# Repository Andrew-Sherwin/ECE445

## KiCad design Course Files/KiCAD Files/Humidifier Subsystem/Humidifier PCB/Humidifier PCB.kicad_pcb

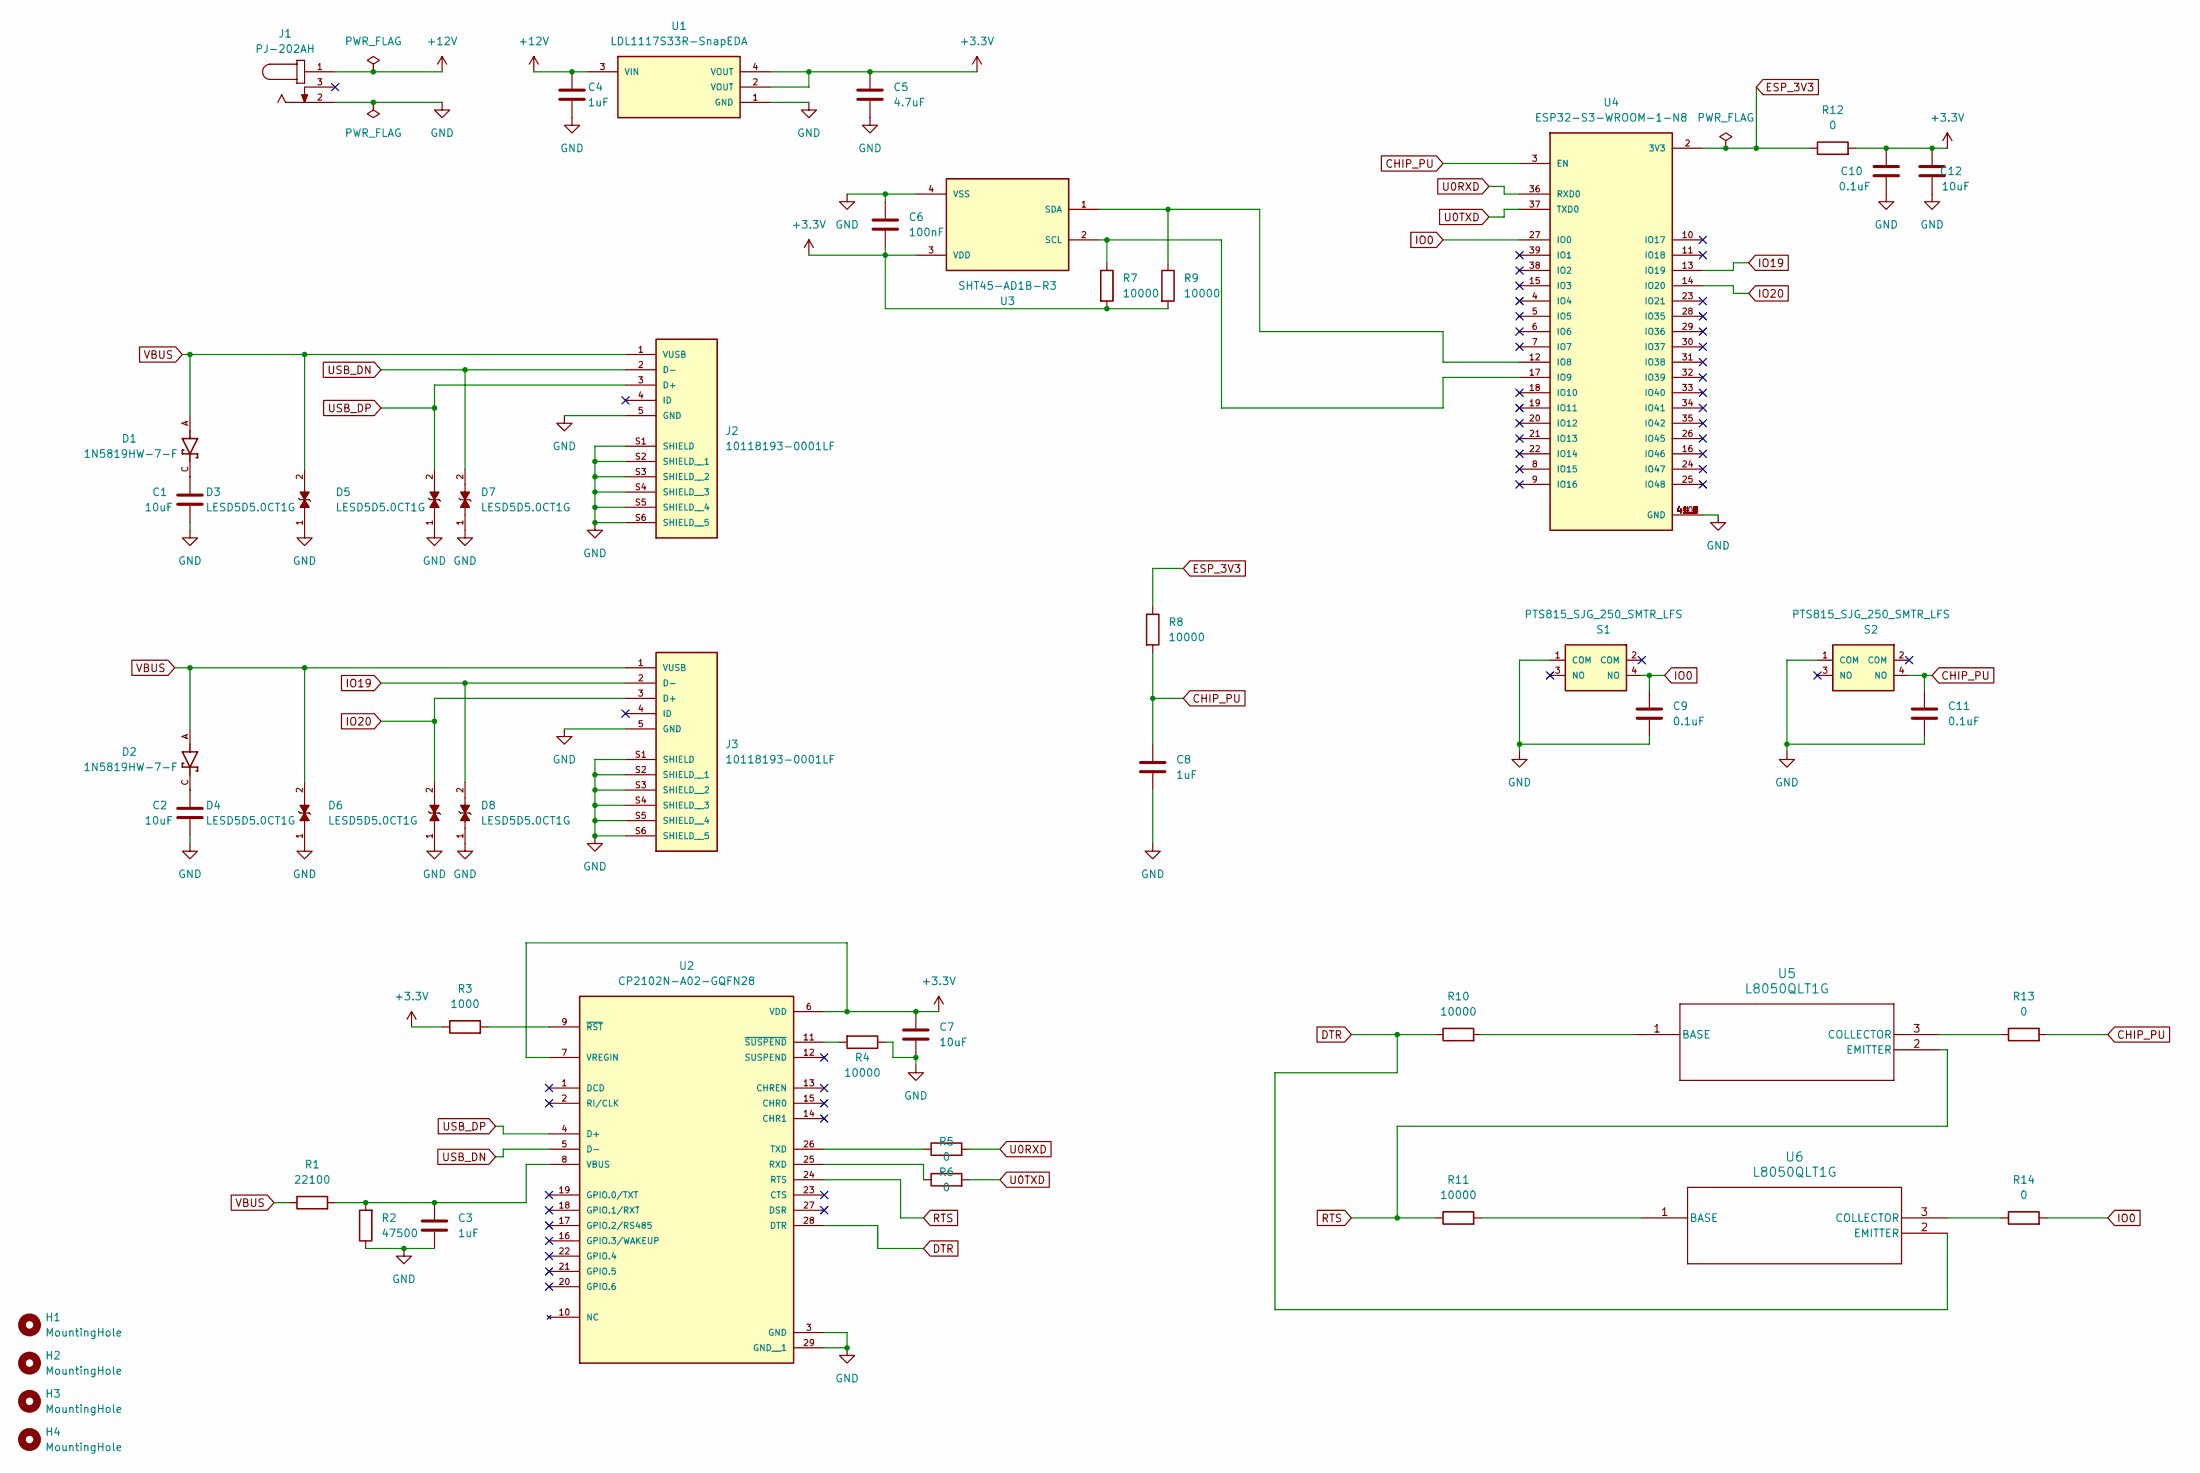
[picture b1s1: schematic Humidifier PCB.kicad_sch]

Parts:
C1, C2, C7, C12: 10uF
C3, C4, C8: 1uF
C5: 4.7uF
C6: 100nF
C9, C10, C11: 0.1uF
D1, D2: 1N5819HW-7-F; PARTREV 18-2
D3, D4, D5, D6, D7, D8: LESD5D5.0CT1G; PARTREV O
H1, H2, H3, H4: MountingHole
J1: PJ-202AH; PART_REV 1.02
J2, J3: 10118193-0001LF; PARTREV E
R1: 22100
R2: 47500
R3: 1000
R4, R7, R8, R9, R10, R11: 10000
R5, R6, R12, R13, R14: 0
S1, S2: PTS815_SJG_250_SMTR_LFS; MOUSER_PART_NUMBER 611-PTS815SJG250SMTR
U1: LDL1117S33R-SnapEDA; PARTREV 7; DigiKey_Part_Number 497-17239-2-ND
U2: CP2102N-A02-GQFN28; PARTREV 1.5
U3: SHT45-AD1B-R3
U4: ESP32-S3-WROOM-1-N8; DigiKey_Part_Number 1965-ESP32-S3-WROOM-1-N8TR-ND
U5, U6: L8050QLT1G

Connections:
+3.3V: C5.1, C6.2, C7.1, C10.1, C12.1, R3.1, R7.2, R9.2, R12.2, U1.2 (VOUT), U1.4 (VOUT), U2.6 (VDD), U2.7 (VREGIN), U3.3 (VDD)
+12V: C4.1, J1.1, U1.3 (VIN)
CHIP_PU: C8.1, C11.1, R8.2, R13.2, S2.4 (NO), U4.3 (EN)
DTR: R10.1, U2.28 (DTR), U6.2 (EMITTER)
ESP_3V3: R8.1, R12.1, U4.2 (3V3)
GND: C1.2, C2.2, C3.2, C4.2, C5.2, C6.1, C7.2, C8.2, C9.2, C10.2, C11.2, C12.2, D3.1, D4.1, D5.1, D6.1, D7.1, D8.1, J1.2, J2.5 (GND), J2.S1 (SHIELD), J2.S2 (SHIELD__1), J2.S3 (SHIELD__2), J2.S4 (SHIELD__3), J2.S5 (SHIELD__4), J2.S6 (SHIELD__5), J3.5 (GND), J3.S1 (SHIELD), J3.S2 (SHIELD__1), J3.S3 (SHIELD__2), J3.S4 (SHIELD__3), J3.S5 (SHIELD__4), J3.S6 (SHIELD__5), R2.1, R4.1, S1.1 (COM), S2.1 (COM), U1.1 (GND), U2.3 (GND), U2.29 (GND__1), U3.4 (VSS), U4.1 (GND), U4.40 (GND), U4.41_1 (GND), U4.41_2 (GND), U4.41_3 (GND), U4.41_4 (GND), U4.41_5 (GND), U4.41_6 (GND), U4.41_7 (GND), U4.41_8 (GND), U4.41_9 (GND)
IO0: C9.1, R14.2, S1.4 (NO), U4.27 (IO0)
IO19: D8.2, J3.2 (D-), U4.13 (IO19)
IO20: D6.2, J3.3 (D+), U4.14 (IO20)
unnamed: C1.1, D1.C
unnamed: C2.1, D2.C
unnamed: R6.1, U2.25 (RXD)
unnamed: R5.1, U2.26 (TXD)
unnamed: C3.1, R1.2, R2.2, U2.8 (VBUS)
unnamed: R3.2, U2.9 (~RST)
unnamed: R4.2, U2.11 (~SUSPEND)
unnamed: R7.1, U3.2 (SCL), U4.17 (IO9)
unnamed: R9.1, U3.1 (SDA), U4.12 (IO8)
unnamed: R10.2, U5.1 (BASE)
unnamed: R13.1, U5.3 (COLLECTOR)
unnamed: R11.2, U6.1 (BASE)
unnamed: R14.1, U6.3 (COLLECTOR)
RTS: R11.1, U2.24 (RTS), U5.2 (EMITTER)
U0RXD: R5.2, U4.36 (RXD0)
U0TXD: R6.2, U4.37 (TXD0)
USB_DN: D7.2, J2.2 (D-), U2.5 (D-)
USB_DP: D5.2, J2.3 (D+), U2.4 (D+)
VBUS: D1.A, D2.A, D3.2, D4.2, J2.1 (VUSB), J3.1 (VUSB), R1.1

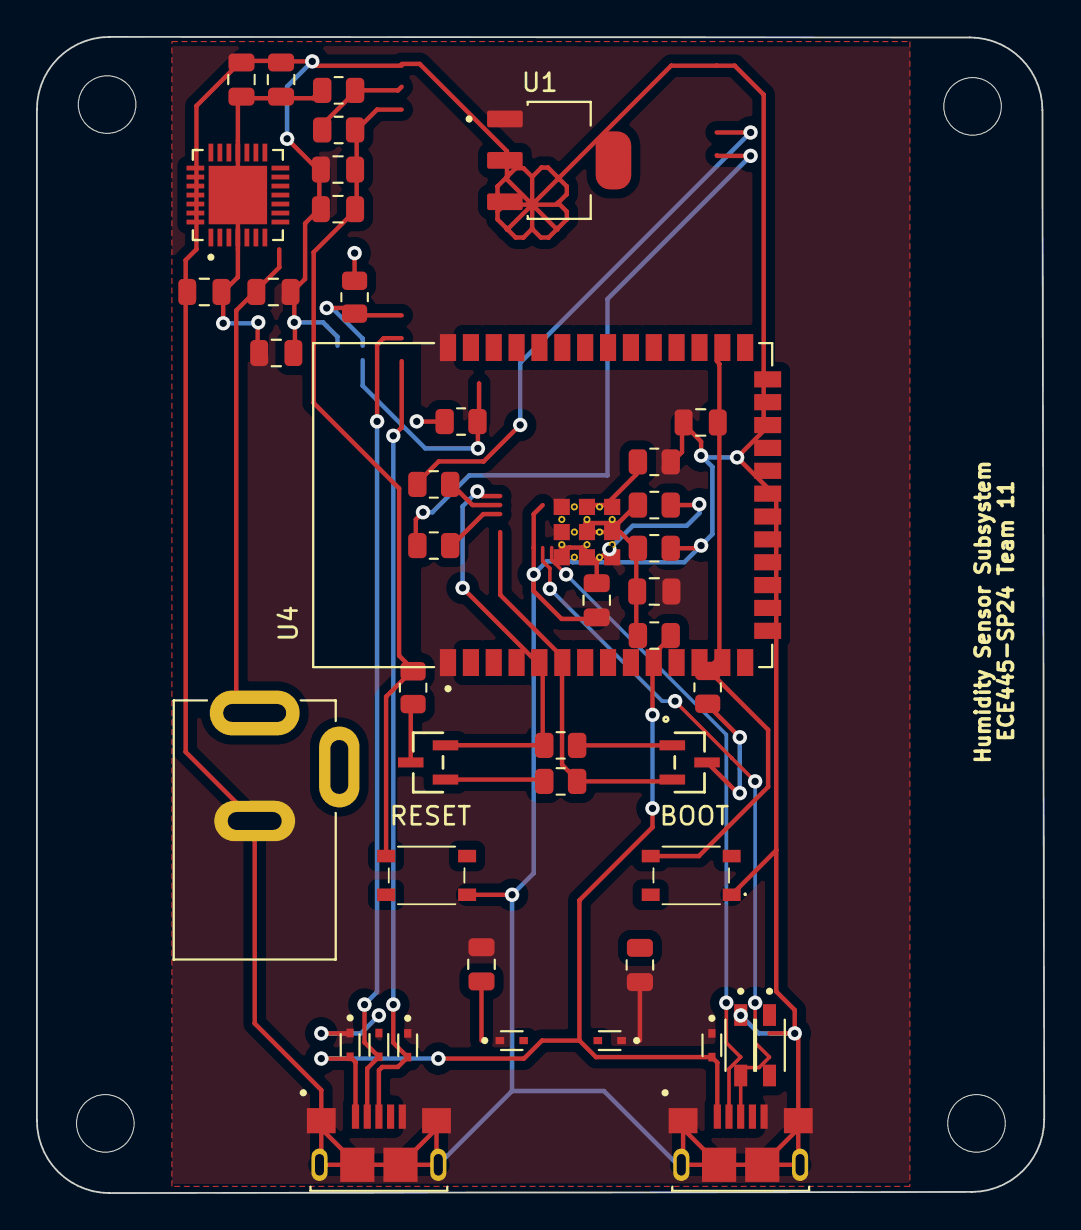
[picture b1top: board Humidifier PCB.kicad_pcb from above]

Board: 2 copper layers, 56.0 x 64.2 mm, 49 parts (1 on the bottom side), 28 nets.

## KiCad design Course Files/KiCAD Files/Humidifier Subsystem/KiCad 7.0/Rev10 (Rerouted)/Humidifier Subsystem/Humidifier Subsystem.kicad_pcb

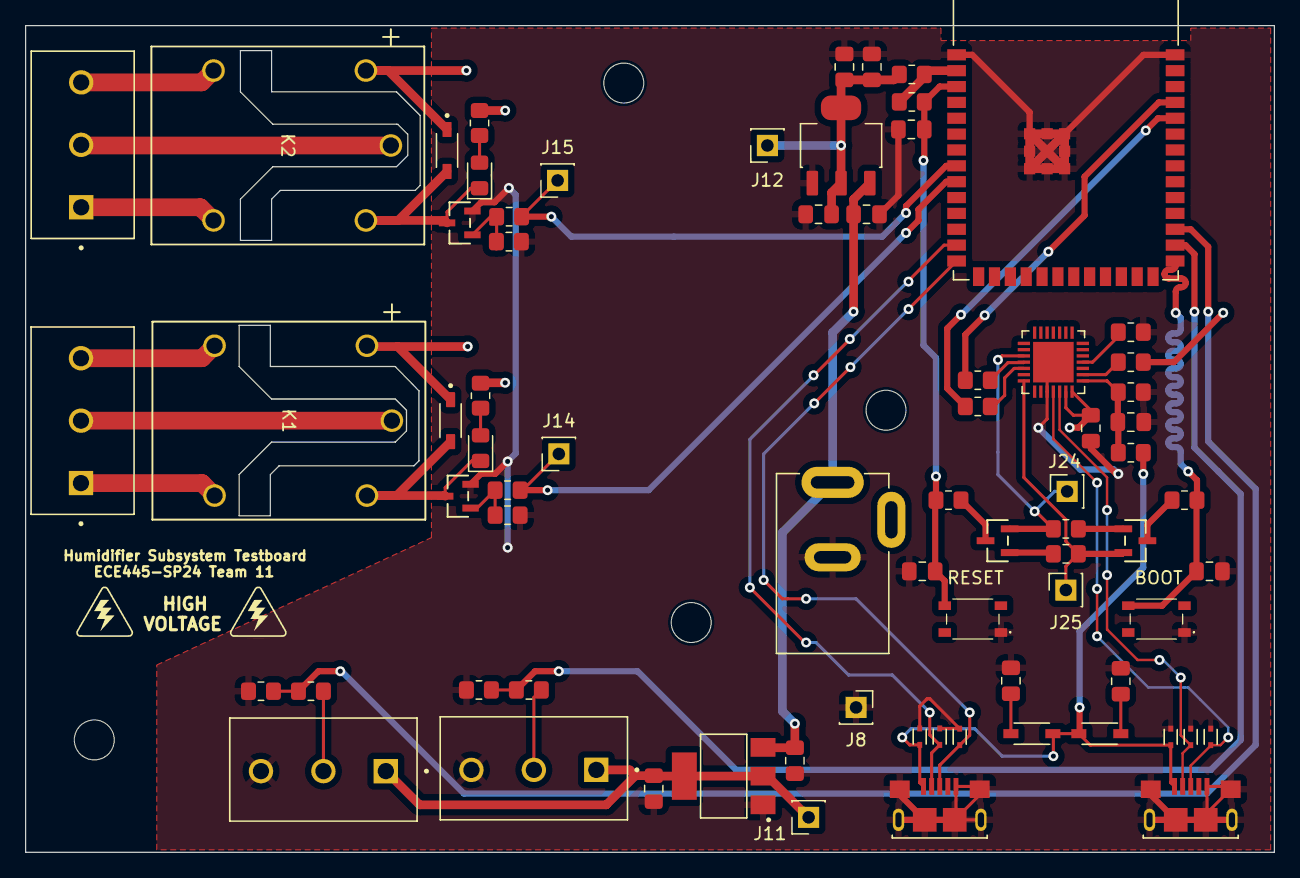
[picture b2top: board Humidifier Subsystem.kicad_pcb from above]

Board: 2 copper layers, 100.0 x 66.2 mm, 77 parts (0 on the bottom side), 45 nets.

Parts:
C1, C3, C9, C10: 1uF; C_0805_2012Metric_Pad1.18x1.45mm_HandSolder
C2, C13: 4.7uF; C_0805_2012Metric_Pad1.18x1.45mm_HandSolder
C4, C6, C7, C8: 10uF; C_0805_2012Metric_Pad1.18x1.45mm_HandSolder
C5, C11, C12: 0.1uF; C_0805_2012Metric_Pad1.18x1.45mm_HandSolder
D1, D2, D3, D4, D7, D8: LESD5D5.0CT1G; LESD5D5_0CT1G
D5, D6: 1N5819HW-7-F
D9, D11: 1N4148W-13-F
D10, D12: LED; D_0805_2012Metric_Pad1.15x1.40mm_HandSolder
H1, H2, H3, H4: MountingHole; MountingHole_3.2mm_M3
J1: PJ-202AH
J2, J3: 10118193-0001LF
J4, J5: Water Level Sensor; 1935174
J6, J7: 1935174
J8: GND Test Probe; PinSocket_1x01_P2.54mm_Vertical
J11, J12, J14, J15, J24, J25: Conn_01x01; PinSocket_1x01_P2.54mm_Vertical
K1, K2: G5LE-14 DC3; G5LE-1 DC3
R1, R4, R9, R10, R14, R23: 10000; R_0805_2012Metric_Pad1.20x1.40mm_HandSolder
R2, R3, R19, R22, R24: 1000; R_0805_2012Metric_Pad1.20x1.40mm_HandSolder
R5: 22100; R_0805_2012Metric_Pad1.20x1.40mm_HandSolder
R6: 47500; R_0805_2012Metric_Pad1.20x1.40mm_HandSolder
R7, R8, R11, R12, R13: 0; R_0805_2012Metric_Pad1.20x1.40mm_HandSolder
R15, R16: 100; R_0805_2012Metric_Pad1.20x1.40mm_HandSolder
R17, R18: 200; R_0805_2012Metric_Pad1.20x1.40mm_HandSolder
S1, S2: PTS815_SJG_250_SMTR_LFS; PTS815 SJG 250 SMTR LFS
U1: ESP32-S3-WROOM-1-N8; ESP32-S3-WROOM-1-N8-SnapEDA
U2: LDL1117S33R-SnapEDA
U3: LDL1117S50R
U4: CP2102N-A02-GQFN28
U5, U6: L8050QLT1G; SOT-23_ONS
U7, U10: MMBT2222LT1G

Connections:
+3.3V: C2.1, C4.1, C5.1, C8.1, D9.C, D11.C, J12.1, K1.2, K2.2, R3.1, R13.2, R19.2, R24.2, U2.2 (VOUT), U2.4 (VOUT), U4.6 (VDD), U4.7 (VREGIN)
+5V: C13.1, J4.1, J5.1, J11.1, U3.2 (VOUT), U3.4 (VOUT-1)
+12V: C1.1, C3.1, J1.1, U2.3 (VIN), U3.3 (VIN)
CHIP_PU: C10.1, C12.1, R11.2, R14.2, S2.4 (NO), U1.3 (EN)
COM_Main: J6.2, K1.1
COM_Main_DC: J7.2, K2.1
DTR: J25.1, R9.1, U4.28 (DTR), U6.2 (EMITTER)
ESP_3V3: R13.1, R14.1, U1.2 (3V3)
Fan_A: J6.3, K1.3
Fan_A_DC: J7.3, K2.3
Fan_B: J6.1, K1.4
Fan_B_DC: J7.1, K2.4
GND: C1.2, C2.2, C3.2, C4.2, C5.2, C6.2, C7.2, C8.2, C9.2, C10.2, C11.2, C12.2, C13.2, D1.1, D2.1, D3.1, D4.1, D7.1, D8.1, J1.2, J2.5 (GND), J2.S1 (SHIELD), J2.S2 (SHIELD__1), J2.S3 (SHIELD__2), J2.S4 (SHIELD__3), J2.S5 (SHIELD__4), J2.S6 (SHIELD__5), J3.5 (GND), J3.S1 (SHIELD), J3.S2 (SHIELD__1), J3.S3 (SHIELD__2), J3.S4 (SHIELD__3), J3.S5 (SHIELD__4), J3.S6 (SHIELD__5), J4.3, J5.3, J8.1, R1.2, R4.1, R6.1, R17.2, R18.2, R23.2, S1.1 (COM), S2.1 (COM), U1.1 (GND), U1.40 (GND), U1.41_1 (GND), U1.41_2 (GND), U1.41_3 (GND), U1.41_4 (GND), U1.41_5 (GND), U1.41_6 (GND), U1.41_7 (GND), U1.41_8 (GND), U1.41_9 (GND), U2.1 (GND), U3.1 (GND), U4.3 (GND), U4.29 (GND__1), U7.2 (EMITTER), U10.2 (EMITTER)
IO0: C11.1, R12.2, S1.4 (NO), U1.27 (IO0)
IO19: D4.2, J3.2 (D-), U1.13 (IO19)
IO20: D3.2, J3.3 (D+), U1.14 (IO20)
unnamed: C6.1, D6.C
unnamed: C7.1, D5.C
unnamed: D10.2 (A), R19.1
unnamed: D9.A, D10.1 (K), K1.5, U7.3 (COLLECTOR)
unnamed: D12.2 (A), R24.1
unnamed: D11.A, D12.1 (K), K2.5, U10.3 (COLLECTOR)
unnamed: J4.2, R15.2
unnamed: J5.2, R16.2
unnamed: R15.1, R17.1, U1.28 (IO35)
unnamed: R16.1, R18.1, U1.29 (IO36)
unnamed: R8.1, U4.25 (RXD)
unnamed: R7.1, U4.26 (TXD)
unnamed: C9.1, R5.2, R6.2, U4.8 (VBUS)
unnamed: R3.2, U4.9 (~RST)
unnamed: R4.2, U4.11 (~SUSPEND)
unnamed: R9.2, U5.1 (BASE)
unnamed: R11.1, U5.3 (COLLECTOR)
unnamed: R10.2, U6.1 (BASE)
unnamed: R12.1, U6.3 (COLLECTOR)
unnamed: R1.1, R2.2, U7.1 (BASE)
unnamed: R22.2, R23.1, U10.1 (BASE)
RTS: J24.1, R10.1, U4.24 (RTS), U5.2 (EMITTER)
Relay_Signal_ACDC: J14.1, R2.1, U1.9 (IO16)
Relay_Signal_DCDC: J15.1, R22.1, U1.8 (IO15)
U0RXD: R7.2, U1.36 (RXD0)
U0TXD: R8.2, U1.37 (TXD0)
USB_DN: D2.2, J2.2 (D-), U4.5 (D-)
USB_DP: D1.2, J2.3 (D+), U4.4 (D+)
VBUS: D5.A, D6.A, D7.2, D8.2, J2.1 (VUSB), J3.1 (VUSB), R5.1
